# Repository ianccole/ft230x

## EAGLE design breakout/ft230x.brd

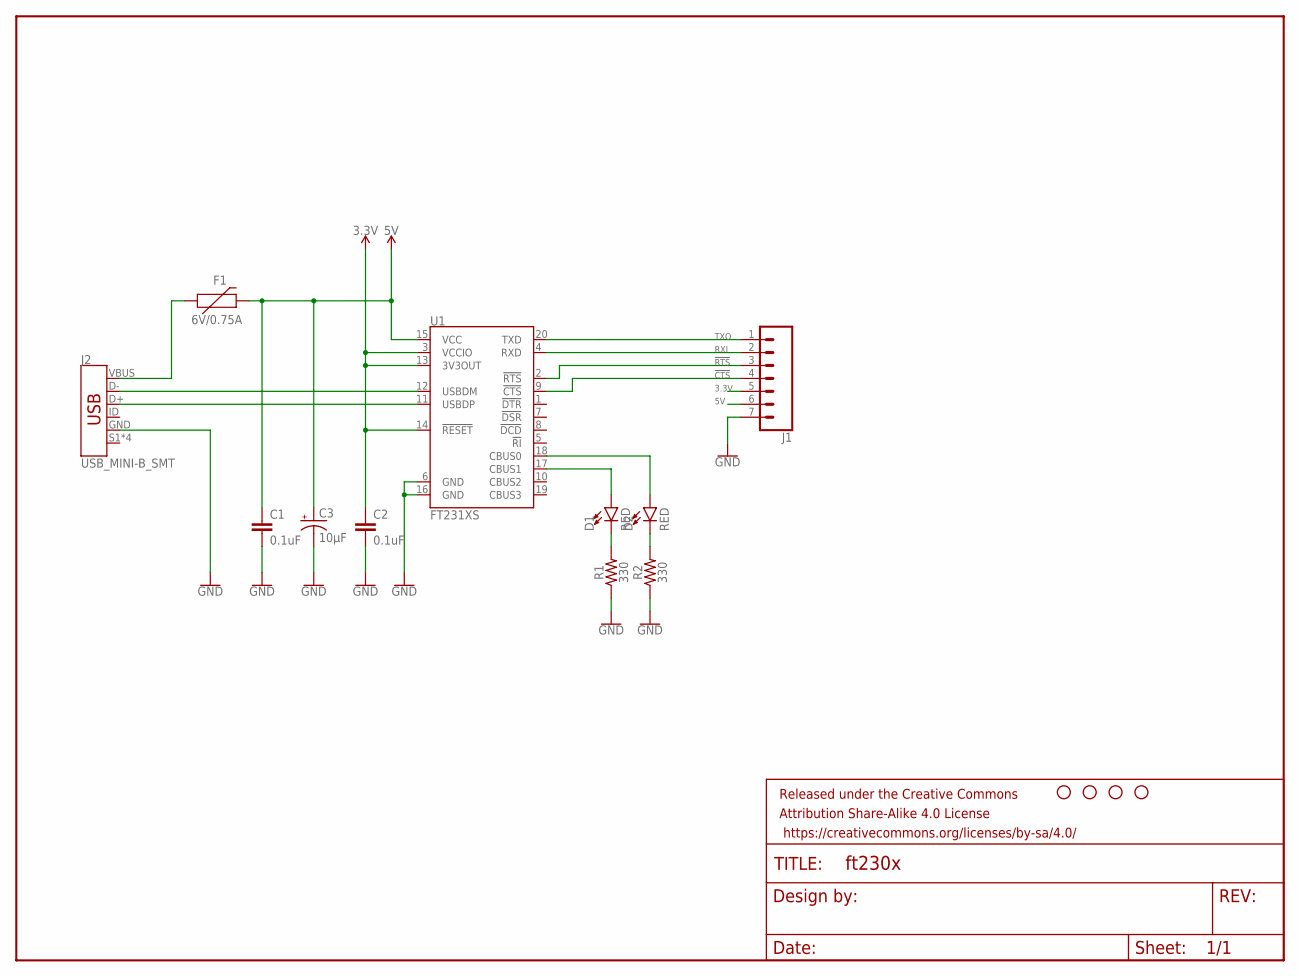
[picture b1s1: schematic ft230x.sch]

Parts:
C1, C2: 0.1uF; 0603
C3: 10µF; EIA6032-NOM
D1, D2: RED; LED-0603
F1: 6V/0.75A; 1206
FRAME1: FRAME-LETTER; CREATIVE_COMMONS
H1, H2, H3, H4: STAND-OFF
J1: CONN_07; 1X07
J2: USB_MINI-B_SMT; USB-MINIB
R1, R2: 330; 0603
U1: FT231XS; SSOP20_L

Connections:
3.3V: C2.1, J1.5, U1.3 (VCCIO), U1.13 (3V3OUT), U1.14 (!RESET)
5V: C1.1, C3.A (+), F1.2, J1.6, U1.15 (VCC)
!CTS: J1.4, U1.9 (!CTS)
!RTS: J1.3, U1.2 (!RTS)
GND: C1.2, C2.2, C3.C (-), J1.7, J2.GND, R1.1, R2.1, U1.6 (GND), U1.16 (GND)
unnamed: D1.C, R1.2
unnamed: D2.C, R2.2
unnamed: F1.1, J2.VBUS
unnamed: D1.A, U1.17 (CBUS1)
unnamed: D2.A, U1.18 (CBUS0)
unnamed: J2.D-, U1.12 (USBDM)
unnamed: J2.D+, U1.11 (USBDP)
RXI: J1.2, U1.4 (RXD)
TXO: J1.1, U1.20 (TXD)

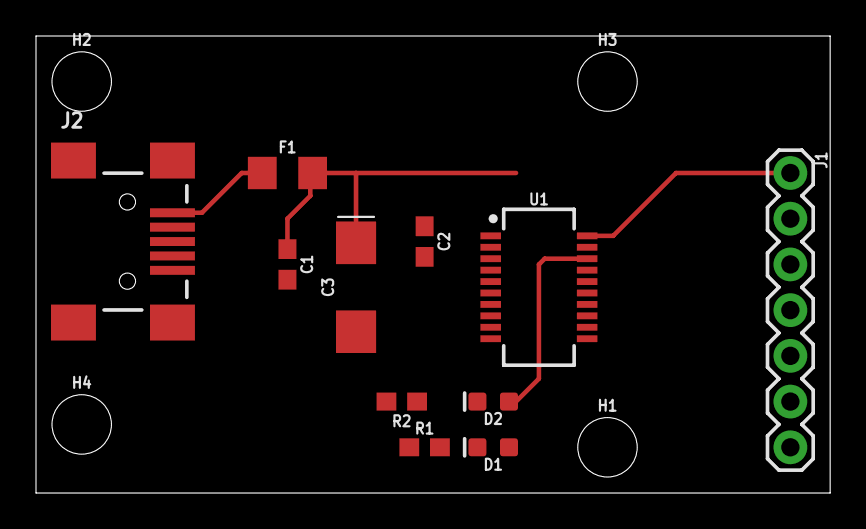
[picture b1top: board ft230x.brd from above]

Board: 2 copper layers, 44.1 x 25.4 mm, 16 parts (0 on the bottom side), 14 nets.

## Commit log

2020-07-10 nitial

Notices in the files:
parts and their libraries:
SparkFun-Capacitors: Licensing: Creative Commons ShareAlike 4.0 International - https://creativecommons.org/licenses/by-sa/4.0
SparkFun-Aesthetics: Released under the Creative Commons Attribution Share-Alike 4.0 License
SparkFun-Aesthetics: https://creativecommons.org/licenses/by-sa/4.0
